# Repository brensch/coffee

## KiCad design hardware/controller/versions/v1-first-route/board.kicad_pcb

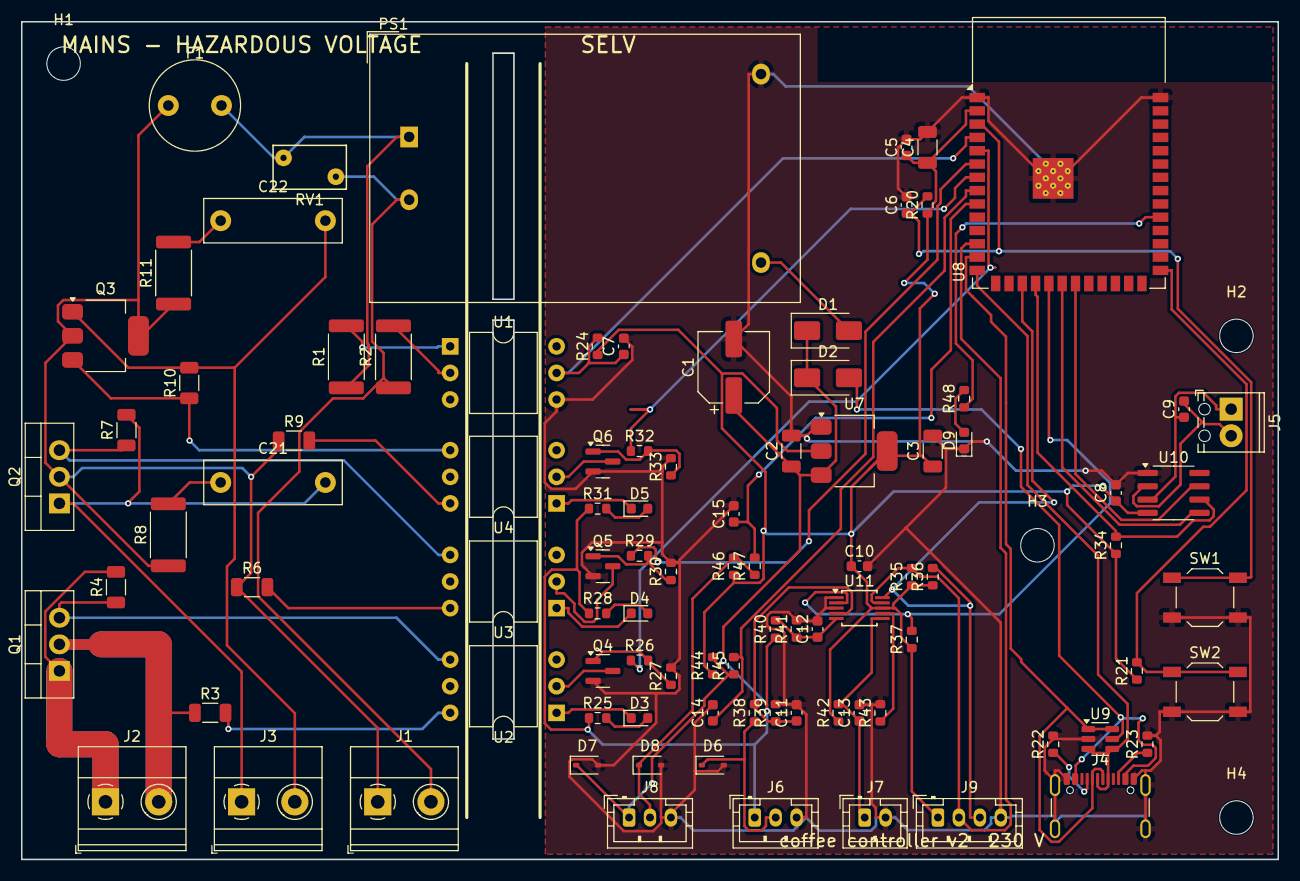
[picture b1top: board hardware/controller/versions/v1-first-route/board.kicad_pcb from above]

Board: 2 copper layers, 120.0 x 80.0 mm, 98 parts (0 on the bottom side), 63 nets.

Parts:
C1: 100uF 16V; CP_Elec_6.3x7.7
C2, C4: 10uF; C_1206_3216Metric
C3: 22uF 6.3V; C_1206_3216Metric
C5, C8, C10, C11, C12, C13, C14, C15: 100nF; C_0603_1608Metric
C6: 1uF; C_0603_1608Metric
C7: 100pF; C_0603_1608Metric
C9: 10nF; C_0603_1608Metric
C21, C22: 10nF X2; C_Rect_L13.0mm_W4.0mm_P10.00mm_FKS3_FKP3_MKS4
D1, D2: SS14; D_SMA
D3: heater green; LED_0603_1608Metric
D4: pump green; LED_0603_1608Metric
D5: valve green; LED_0603_1608Metric
D6, D7, D8: PESD5V0S1BA; D_SOD-323
D9: status blue; LED_0603_1608Metric
F1: T500mA; Fuse_Littelfuse_372_D8.50mm
H1, H2, H3, H4: M3; MountingHole_3.2mm_M3
J1: Mains in; TerminalBlock_Phoenix_MKDS-1,5-2-5.08_1x02_P5.08mm_Horizont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
J2: Heater; TerminalBlock_Phoenix_MKDS-1,5-2-5.08_1x02_P5.08mm_Horizont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
J3: Pump / valve; TerminalBlock_Phoenix_MKDS-1,5-2-5.08_1x02_P5.08mm_Horizont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
J4: USB-C; USB_C_Receptacle_GCT_USB4105-xx-A_16P_TopMnt_Horizontal
J5: Thermocouple K; TerminalBlock_Phoenix_MPT-0,5-2-2.54_1x02_P2.54mm_Horizontal
J6: Pressure 0-1.6MPa; JST_PH_B3B-PH-K_1x03_P2.00mm_Vertical
J7: Group NTC (opt); JST_PH_B2B-PH-K_1x02_P2.00mm_Vertical
J8: Switches; JST_PH_B3B-PH-K_1x03_P2.00mm_Vertical
J9: I2C expansion; JST_PH_B4B-PH-K_1x04_P2.00mm_Vertical
PS1: HLK-5M05; Converter_ACDC_Hi-Link_HLK-5Mxx
Q1: BTA16-600BW; TO-220-3_Vertical
Q2: BTA08-600CW; TO-220-3_Vertical
Q3: Z0109MN; SOT-223-3_TabPin2
Q4, Q5, Q6: AO3400A; SOT-23
R1, R2: 47k 1W; R_2512_6332Metric
R3, R6, R9: 360; R_1206_3216Metric
R4, R7, R10: 330; R_1206_3216Metric
R8, R11: 100 1W; R_2512_6332Metric
R20, R21, R34, R37, R44, R46: 10k; R_0603_1608Metric
R22, R23: 5.1k; R_0603_1608Metric
R24: 47k; R_0603_1608Metric
R25, R28, R31: 150; R_0603_1608Metric
R26, R29, R32: 100; R_0603_1608Metric
R27, R30, R33, R43: 100k; R_0603_1608Metric
R35, R36: 4.7k; R_0603_1608Metric
R38, R40, R42: 10k 0.1%; R_0603_1608Metric
R39, R41: 20k 0.1%; R_0603_1608Metric
R45, R47, R48: 1k; R_0603_1608Metric
RV1: 10D561K; RV_Disc_D7mm_W4.2mm_P5mm
SW1: RESET; SW_SPST_TL3342
SW2: BOOT; SW_SPST_TL3342
U1: H11AA1; DIP-6_W10.16mm
U2, U3, U4: MOC3063; DIP-6_W10.16mm
U7: AMS1117-3.3; SOT-223-3_TabPin2
U8: ESP32-S3-WROOM-1-N8; ESP32-S3-WROOM-1
U9: USBLC6-2SC6; SOT-23-6
U10: MAX31855KASA+; SOIC-8_3.9x4.9mm_P1.27mm
U11: ADS1115IDGSR; MSOP-10_3x3mm_P0.5mm

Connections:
5V_PSU: D1.2, PS1.4
+3V3: C3.1, C4.1, C5.1, C8.1, C10.1, J9.1, R20.1, R21.1, R24.1, R34.1, R35.1, R36.1, R37.1, R42.1, R44.1, R46.1, U7.2, U8.2, U10.4, U11.8
+5V: C1.1, C2.1, D1.1, D2.1, J6.1, R25.1, R28.1, R31.1, R40.1, U7.3
AC_L: F1.1, J1.1, Q2.2, Q3.2, R6.1, R8.1, R9.1, R11.1
AC_L_FUSED: F1.2, PS1.1, R1.1, RV1.1
AC_N: J1.2, PS1.2, R2.1, RV1.2
ADC_RDY: R37.2, U8.19, U11.2
AIN3_SPARE: R43.1, U11.7
CC1: J4.A5, R22.1
CC2: J4.B5, R23.1
EN: C6.1, R20.2, SW1.1, U8.3
GND: C1.2, C2.2, C3.2, C4.2, C5.2, C6.2, C7.2, C8.2, C10.2, C11.2, C12.2, C13.2, C14.2, C15.2, D6.2, D7.2, D8.2, D9.1, J4.A1, J4.A12, J4.B1, J4.B12, J4.S1, J6.3, J7.2, J8.3, J9.4, PS1.3, Q4.2, Q5.2, Q6.2, R22.2, R23.2, R27.2, R30.2, R33.2, R39.2, R41.2, R43.2, SW1.2, SW2.2, U1.4, U7.1, U8.1, U8.40, U8.41, U9.2, U10.1, U11.1, U11.3
HEATER_CMD: R26.1, U8.5
HEATER_DRV: Q4.3, U2.2
HEATER_G: Q4.1, R26.2, R27.1
HEATER_GATE: Q1.3, R4.1, U2.4
HEATER_LED_A: D3.2, R25.2
HEATER_LED_K: D3.1, U2.1
HEATER_OPTO: R3.2, U2.6
HTR_A: J2.1, Q1.1, R4.2
HTR_B: J2.2, Q1.2, R3.1
IO0_BOOT: R21.2, SW2.1, U8.27
NTC_AIN2: C13.1, J7.1, R42.2, U11.6
PUMP_CMD: R29.1, U8.6
PUMP_DRV: Q5.3, U3.2
PUMP_G: Q5.1, R29.2, R30.1
PUMP_GATE: Q2.3, R7.1, U3.4
PUMP_L: C21.2, J3.1, Q2.1, R7.2
PUMP_LED_A: D4.2, R28.2
PUMP_LED_K: D4.1, U3.1
PUMP_OPTO: R6.2, U3.6
PUMP_SNUB: C21.1, R8.2
P_AIN0: C11.1, R38.2, R39.1, U11.4
P_SIG: D6.1, J6.2, R38.1
SCL: J9.3, R36.2, U8.17, U11.10
SDA: J9.2, R35.2, U8.12, U11.9
STATUS: R48.1, U8.31
STATUS_A: D9.2, R48.2
SW_BREW: D7.1, J8.1, R44.2, R45.1
SW_BREW_IN: C14.1, R45.2, U8.8
SW_STEAM: D8.1, J8.2, R46.2, R47.1
SW_STEAM_IN: C15.1, R47.2, U8.9
TC+: C9.1, J5.1, U10.3
TC-: C9.2, J5.2, U10.2
TC_CS: R34.2, U8.18, U10.6
TC_SCK: U8.20, U10.5
TC_SO: U8.21, U10.7
USB_D+: J4.A6, J4.B6, U8.14, U9.3, U9.4
USB_D-: J4.A7, J4.B7, U8.13, U9.1, U9.6
V5_AIN1: C12.1, R40.2, R41.1, U11.5
VALVE_CMD: R32.1, U8.7
VALVE_DRV: Q6.3, U4.2
VALVE_G: Q6.1, R32.2, R33.1
VALVE_GATE: Q3.3, R10.1, U4.4
VALVE_L: C22.2, J3.2, Q3.1, R10.2
VALVE_LED_A: D5.2, R31.2
VALVE_LED_K: D5.1, U4.1
VALVE_OPTO: R9.2, U4.6
VALVE_SNUB: C22.1, R11.2
VBUS: D2.2, J4.A4, J4.A9, J4.B4, J4.B9, U9.5
ZC: C7.1, R24.2, U1.5, U8.4
ZC_A: R1.2, U1.1
ZC_B: R2.2, U1.2

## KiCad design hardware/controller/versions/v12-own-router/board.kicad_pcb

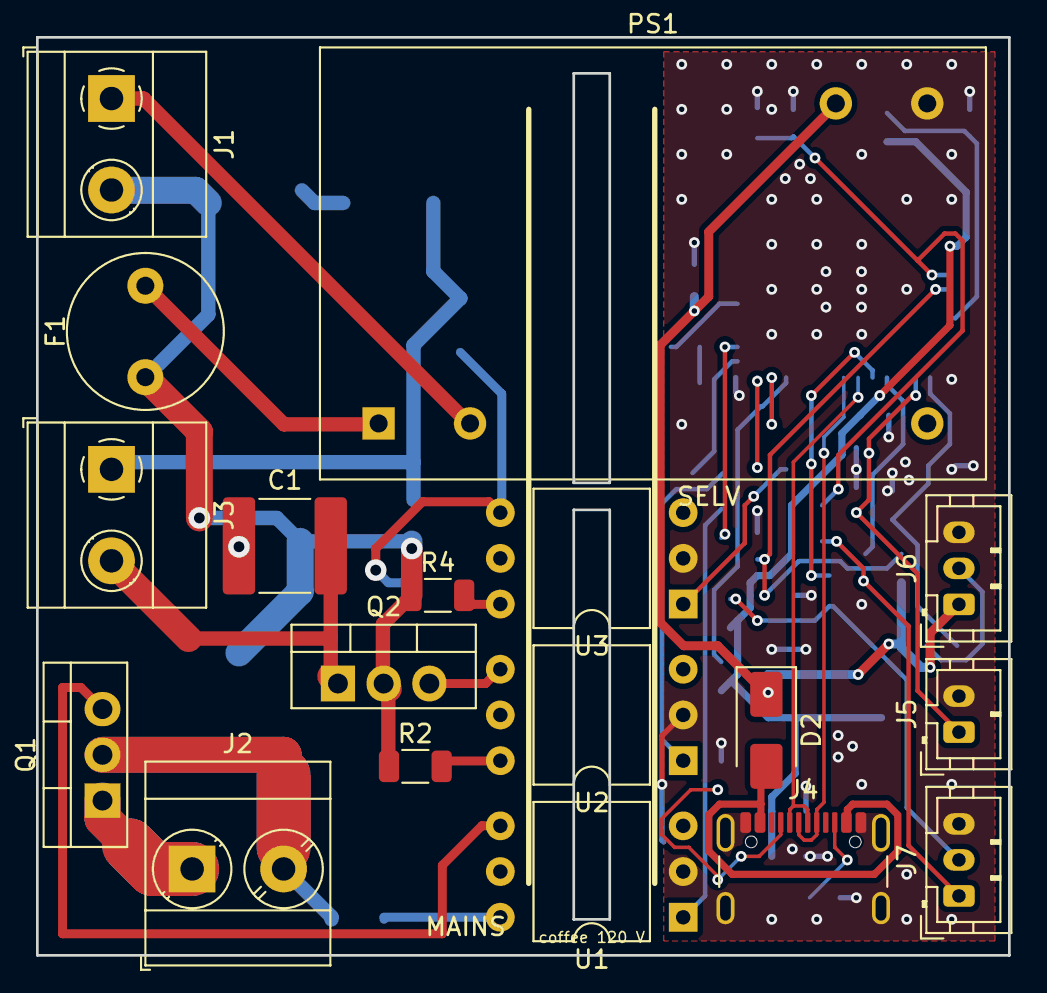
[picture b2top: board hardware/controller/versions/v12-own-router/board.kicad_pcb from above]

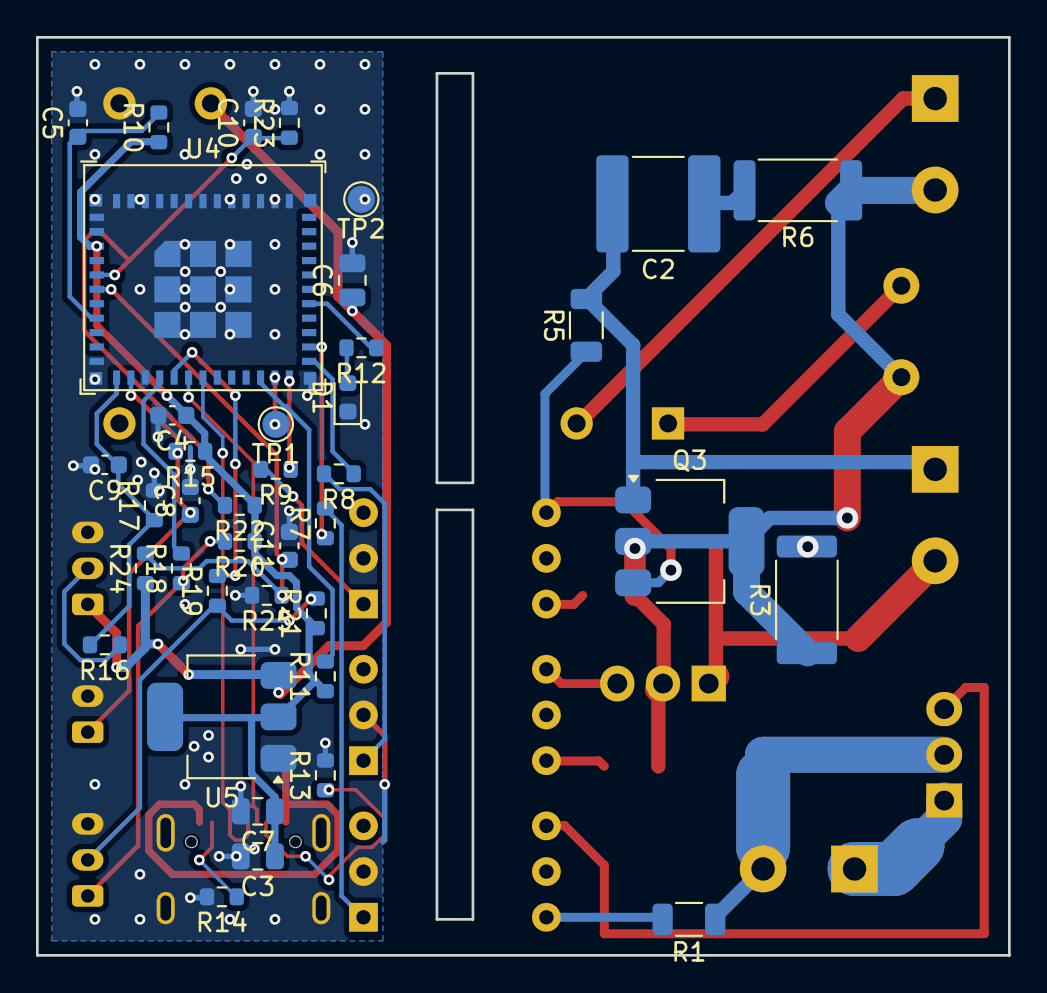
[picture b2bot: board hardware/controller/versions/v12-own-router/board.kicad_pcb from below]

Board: 2 copper layers, 54.0 x 51.0 mm, 57 parts (39 on the bottom side), 43 nets.

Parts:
C1, C2: 10nF X2; C_2220_5750Metric
C3: 10uF 10V X7R; C_0805_2012Metric
C4: 100nF X7R; C_0603_1608Metric
C5: 1uF X7R; C_0603_1608Metric
C6, C7: 22uF 10V X7R; C_0805_2012Metric
C8, C9, C10, C11: 100nF; C_0603_1608Metric
D1: green; LED_0603_1608Metric
D2: SS14; D_SMA
F1: T500mA; Fuse_Littelfuse_372_D8.50mm
J1: Mains in; TerminalBlock_Phoenix_MKDS-1,5-2-5.08_1x02_P5.08mm_Horizont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
J2: Heater; TerminalBlock_Phoenix_MKDS-3-2-5.08_1x02_P5.08mm_Horizontal
J3: Valve / pump; TerminalBlock_Phoenix_MKDS-1,5-2-5.08_1x02_P5.08mm_Horizont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
J4: USB-C; USB_C_Receptacle_GCT_USB4105-xx-A_16P_TopMnt_Horizontal
J5: Thermistor; JST_PH_B2B-PH-K_1x02_P2.00mm_Vertical
J6: Pressure; JST_PH_B3B-PH-K_1x03_P2.00mm_Vertical
J7: Switches; JST_PH_B3B-PH-K_1x03_P2.00mm_Vertical
PS1: RAC03E-05SK/277; RAC03E-K_277
Q1: BTA24-800BW; TO-220-3_Vertical
Q2: BTA08-800BW; TO-220-3_Vertical
Q3: Z0109NN; SOT-223-3_TabPin2
R1, R2, R4: 360; R_1206_3216Metric
R3, R6: 100 1W; R_2512_6332Metric
R5: 330; R_1206_3216Metric
R7, R8, R9: 150; R_0603_1608Metric
R10, R11: 10k; R_0603_1608Metric
R12: 100; R_0603_1608Metric
R13, R14: 5.1k; R_0603_1608Metric
R15: 8.2k 0.1%; R_0603_1608Metric
R16, R22, R23, R25: 10k 0.1%; R_0603_1608Metric
R17, R24: 20k 0.1%; R_0603_1608Metric
R18, R19: 1k; R_0603_1608Metric
R20, R21: 4.7k; R_0603_1608Metric
TP1: BOOT; TestPoint_Pad_D1.5mm
TP2: GND; TestPoint_Pad_D1.5mm
U1, U2, U3: MOC3083; DIP-6_W10.16mm
U4: ESP32-C6-MINI-1U-H4; ESP32-C6-MINI-1U
U5: TLV1117LV33; SOT-223-3_TabPin2

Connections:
+3V3: C3.1, C4.1, C7.1, R10.1, R11.1, R15.1, R20.1, R21.1, R22.1, U4.3, U5.2
+5V: C6.1, D2.1, J6.1, PS1.5, R24.1, U5.3
AC_L: F1.1, J1.2, Q2.2, Q3.2, R2.1, R3.1, R4.1, R6.1
AC_L_FUSED: F1.2, PS1.1
AC_N: J1.1, PS1.2
CC1: J4.A5, R13.1
CC2: J4.B5, R14.1
EN: C5.1, R10.2, U4.8
GND: C3.2, C4.2, C5.2, C6.2, C7.2, C8.2, C9.2, C10.2, C11.2, D1.1, J4.A1, J4.A12, J4.B1, J4.B12, J4.S1, J5.2, J6.3, J7.3, PS1.4, R13.2, R14.2, R17.2, R23.2, R25.2, TP2.1, U1.2, U2.2, U3.2, U4.1, U4.2, U4.11, U4.14, U4.36, U4.37, U4.38, U4.39, U4.40, U4.41, U4.42, U4.43, U4.44, U4.45, U4.46, U4.47, U4.48, U4.49, U4.50, U4.51, U4.52, U4.53, U5.1
HEATER_CMD: R7.1, U4.26
HEATER_GATE: Q1.3, U1.4
HEATER_OPTO: R1.2, U1.6
HEATER_OPTO_A: R7.2, U1.1
HTR_A: J2.1, Q1.1
HTR_B: J2.2, Q1.2, R1.1
IO8_STRAP: R11.2, U4.22
IO9_BOOT: TP1.1, U4.23
NTC: C8.1, J5.1, R15.2, U4.13
PUMP_CMD: R8.1, U4.25
PUMP_GATE: Q2.3, U2.4
PUMP_L: C1.2, J3.2, Q2.1
PUMP_OPTO: R2.2, U2.6
PUMP_OPTO_A: R8.2, U2.1
PUMP_SNUB: C1.1, R3.2
P_ADC: C9.1, R16.2, R17.1, U4.12
P_SIG: J6.2, R16.1
STATUS: R12.1, U4.29
STATUS_A: D1.2, R12.2
SW_BREW: R18.2, U4.15
SW_BREW_IN: J7.1, R18.1, R20.2
SW_STEAM: R19.2, U4.16
SW_STEAM_IN: J7.2, R19.1, R21.2
USB_D+: J4.A6, J4.B6, U4.18
USB_D-: J4.A7, J4.B7, U4.17
V3_SNS: C10.1, R22.2, R23.1, U4.5
V5_SNS: C11.1, R24.2, R25.1, U4.6
VALVE_CMD: R9.1, U4.24
VALVE_GATE: Q3.3, R5.1, U3.4
VALVE_L: C2.2, J3.1, Q3.1, R5.2
VALVE_OPTO: R4.2, U3.6
VALVE_OPTO_A: R9.2, U3.1
VALVE_SNUB: C2.1, R6.2
VBUS: D2.2, J4.A4, J4.A9, J4.B4, J4.B9

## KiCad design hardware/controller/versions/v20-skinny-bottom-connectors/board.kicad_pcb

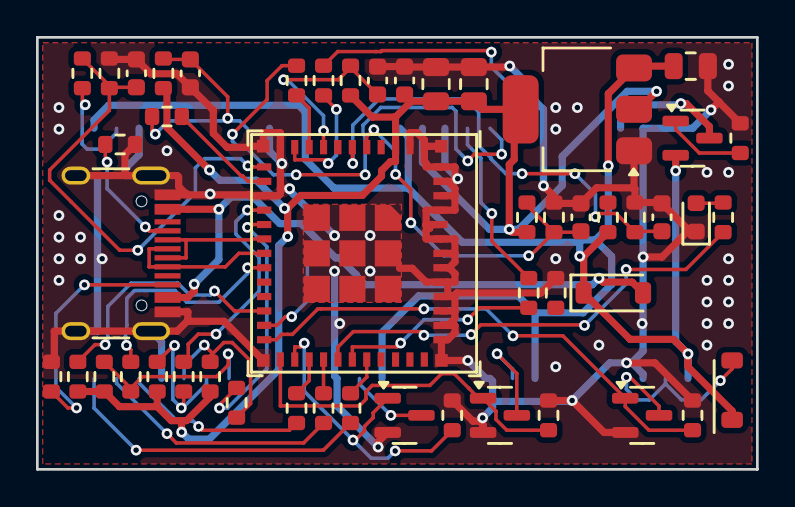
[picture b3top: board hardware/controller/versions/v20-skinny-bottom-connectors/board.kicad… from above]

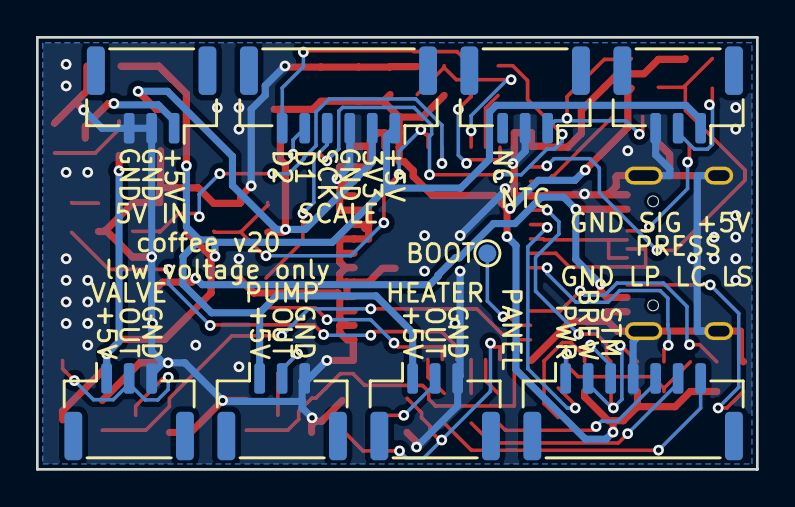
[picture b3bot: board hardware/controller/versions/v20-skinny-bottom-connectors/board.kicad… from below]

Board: 2 copper layers, 40.0 x 24.0 mm, 58 parts (9 on the bottom side), 45 nets.

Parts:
C3: 10uF 25V X5R; C_0805_2012Metric
C4, C8, C10, C11: 100nF X7R; C_0603_1608Metric
C5: 1uF X5R; C_0603_1608Metric
C6, C7: 22uF 25V X5R; C_0805_2012Metric
C9: 22nF X7R; C_0603_1608Metric
D1: red; LED_0603_1608Metric
D2: B5819W; D_SOD-123
D5: 1N4148W; D_SOD-123
J1: 5V in; JST_GH_SM03B-GHS-TB_1x03-1MP_P1.25mm_Horizontal
J2: Heater; JST_GH_SM03B-GHS-TB_1x03-1MP_P1.25mm_Horizontal
J3: Pump; JST_GH_SM03B-GHS-TB_1x03-1MP_P1.25mm_Horizontal
J4: USB-C; USB_C_Receptacle_HRO_TYPE-C-31-M-12
J5: Thermistor; JST_GH_SM03B-GHS-TB_1x03-1MP_P1.25mm_Horizontal
J6: Pressure; JST_GH_SM03B-GHS-TB_1x03-1MP_P1.25mm_Horizontal
J7: Front panel; JST_GH_SM07B-GHS-TB_1x07-1MP_P1.25mm_Horizontal
J8: Valve; JST_GH_SM03B-GHS-TB_1x03-1MP_P1.25mm_Horizontal
J10: Scale; JST_GH_SM06B-GHS-TB_1x06-1MP_P1.25mm_Horizontal
Q1, Q2, Q3: AO3400A; SOT-23
Q4: AO3401A; SOT-23
R4, R5, R6: 3.3k; R_0603_1608Metric
R10, R11, R22, R23, R25, R26, R36: 10k; R_0603_1608Metric
R12, R18, R19, R27, R29: 1k; R_0603_1608Metric
R13, R14: 5.1k; R_0603_1608Metric
R15, R20, R21, R28: 4.7k; R_0603_1608Metric
R16: 47k; R_0603_1608Metric
R17: 100k; R_0603_1608Metric
R24: 20k; R_0603_1608Metric
R30, R31, R32: 330; R_0603_1608Metric
R33, R34, R35: 100; R_0603_1608Metric
TP1: BOOT; TestPoint_Pad_D1.0mm
U4: ESP32-C6-MINI-1U-H4; ESP32-C6-MINI-1U
U5: TLV1117LV33DCYR; SOT-223-3_TabPin2

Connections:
+3V3: C3.1, C4.1, C7.1, J10.2, R10.1, R11.1, R15.1, R20.1, R21.1, R22.1, R28.1, U4.3, U5.2
+5V: C6.1, D2.1, D5.1, J2.1, J3.1, J6.1, J8.1, J10.1, Q4.2, R24.1, U5.3
+5V_IN: J1.1, Q4.3
CC1: J4.A5, R13.1
CC2: J4.B5, R14.1
EN: C5.1, R10.2, U4.8
GND: C3.2, C4.2, C5.2, C6.2, C7.2, C8.2, C9.2, C10.2, C11.2, D1.1, J1.2, J1.3, J2.3, J3.3, J4.A1, J4.A12, J4.B1, J4.B12, J4.S1, J5.2, J6.3, J7.4, J8.3, J10.3, Q1.2, Q2.2, Q3.2, R4.2, R5.2, R6.2, R13.2, R14.2, R17.2, R23.2, R25.2, R26.2, R36.2, U4.1, U4.2, U4.11, U4.14, U4.36, U4.37, U4.38, U4.39, U4.40, U4.41, U4.42, U4.43, U4.44, U4.45, U4.46, U4.47, U4.48, U4.49, U4.50, U4.51, U4.52, U4.53, U5.1
HEATER_CMD: Q1.1, R4.1, U4.26
HEATER_OUT: J2.2, Q1.3
IO8_STRAP: R11.2, U4.22
IO9_BOOT: TP1.1, U4.23
LED_COFFEE: J7.6, R31.2
LED_COFFEE_IO: R31.1, U4.28
LED_PWR: J7.5, R30.2
LED_PWR_IO: R30.1, U4.27
LED_STEAM: J7.7, R32.2
LED_STEAM_IO: R32.1, U4.31
NTC: C8.1, J5.1, R15.2, R27.1
NTC_ADC: R27.2, U4.13
PUMP_CMD: Q2.1, R5.1, U4.25
PUMP_OUT: J3.2, Q2.3
P_ADC: C9.1, R16.2, R17.1, U4.12
P_SIG: J6.2, R16.1
RP_GATE: Q4.1, R26.1
SCALE_DOUT1: R34.1, U4.9
SCALE_DOUT1_IN: J10.5, R34.2
SCALE_DOUT2: R35.1, U4.10
SCALE_DOUT2_IN: J10.6, R35.2
SCALE_SCK: R33.1, U4.30
SCALE_SCK_IN: J10.4, R33.2
STATUS: R12.1, U4.29
STATUS_A: D1.2, R12.2
SW_BREW: R18.2, U4.15
SW_BREW_IN: J7.2, R18.1, R20.2
SW_POWER: R29.2, U4.19
SW_POWER_IN: J7.1, R28.2, R29.1
SW_STEAM: R19.2, U4.16
SW_STEAM_IN: J7.3, R19.1, R21.2
USB_D+: J4.A6, J4.B6, U4.18
USB_D-: J4.A7, J4.B7, U4.17
V3_SNS: C10.1, R22.2, R23.1, U4.5
V5_SNS: C11.1, R24.2, R25.1, U4.6
VALVE_CMD: Q3.1, R6.1, U4.24
VALVE_OUT: D5.2, J8.2, Q3.3
VBUS: D2.2, J4.A4, J4.A9, J4.B4, J4.B9
